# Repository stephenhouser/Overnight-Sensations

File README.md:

# Overnight Sensation Speakers

This repository contains my build plans for [Paul Carmody](https://sites.google.com/site/undefinition/diy?authuser=0)'s **Overnight Sensations** speakers. It is intended to compliment Paul's designs, plans, and notes with manufacturable components. That is herein lie full CNC-able and PCB-producable components.

This currently includes details for the [original bookshelf speakers](https://sites.google.com/site/undefinition/bookshelf-speakers/diy-overnightsensations), the [floorstanding TMM's](https://sites.google.com/site/undefinition/floorstanding-speakers/overnightsensationtmm?authuser=0), and the [center speaker](https://sites.google.com/site/undefinition/home-theater-speakers/overnightsensationcenterchannelbipolewhatwhen?authuser=0). I have future plans to include the [surround speakers](https://sites.google.com/site/undefinition/home-theater-speakers/overnightsensationcenterchannelbipolewhatwhen?authuser=0).

This is a work in progress, bear with me as I build the speakers and add the components.

### A few notes on the designs

- Designed for 1/2" material. Using the 1/2" plans in all cases.
- Uses miter joints at the box corners, so can use already faced plywood.
- Uses painted MDF for the baffle. Could use faced plywood but the fillet on the outside edges would need to be removed.
- Does not use rabbet for back. Seems an overly complicated addition.

If you are using something else, it should be easily adapted.

## Bookshelf TM

No build files available.

I built these a few years ago and did not document things very well, save for a few photos and the build documents.

## Floorstanding TMM

Includes:

- Cabinet Plans in FreeCAD
- Crossover PCB in KiCad with Gerbers for PCB manufacture
- 2"x3" port in FreeCAD for 3D printing

These are the most well developed plans as they are the most recent I've worked on.

NOTE: The version I have designed for uses the HiVi T20 tweeter and 1/2" thick wood for the cabinet. I've made some attempt at making the design general and adaptable, but you will likely have to tweak if you build the alternate version.

The cabinet design was reproduced from Paul's SketchUp screen capture into FreeCAD. The full FreeCAD files are in the [floorstanding[(floorstading)] directory. Here's a snapshot of the major dimensions. Perhaps enough to build from.

My crossover PCB is for the HiVi T20 tweeter. You can use the same PCB, just substitute the different value components.

**NOTE**: I started working on alternate crossovers with thicker traces but stopped. See the notes below about **Power Handling**. I think the 3mm traces I have are "thick enough" for this configuration under normal use. It would be nice to have thicker traces (5-6mm), and 9.5mm spaced screw terminals. If I ever do make another PCB, I'll make those changes. Oh, I also forgot to put in additional holes for the wire ties on the 1.5 mH coil.

## Center MMTM

Next to be built!

## Surround

Yet to be built!

## Software Tools

I use the following software in the production of these. These are all open-source freely available products.

- [Inkscape](https://inkscape.org) for basic drawing and to generate SVG files for patterns.
- [KiCad](https://www.kicad.org) for schematic capture and PCB design.
- [FreeCAD](https://www.freecad.org) for cabinet design and CAM toolpath generation.
- [LibreOffice](https://www.libreoffice.org) for spreadsheets, bill of materials (BOM).

In the past I used the following software in parts of the process but am quickly moving away from them as I migrate to FreeCAD and other more open and interchangable software.

- [Carbide Create](https://carbide3d.com/carbidecreate/) / [Carbide Motion](https://carbide3d.com/carbidemotion/) for 2D CAD/CAM on Shapeoko 3
- [Autodesk Fusion 360](no link, autodesk keeps taking features away and I don't want to support that) for cabinet design and CAM toolpath generation

## Power Handling

To calculate what the power rating of the speaker is, and the appropriate trace width for the crossover boards.

- HiVi B4N is rated 25W RMS (50W max) at 8 Ohms, 60 - 4,000 Hz
- HiVi B3N is rated 10W RMS (30W max) at 8 Ohms, 80 - 12,000 Hz
- HiVi T20-8 is rated 15W RMS (no max specified) at 8 Ohms, 4,000 - 20,000 Hz

From some random source on the Internet:

    roughly 40-40-20 percentage for woofer, mid, tweeter

From [celestion](https://celestion.com/blog/power-handling-all-you-need-to-know/)

    As a rule of thumb, the cabinet power handling should be calculated as a multiple of the lowest rated speaker. For example in a 2×12 containing a 60-watt speaker and a 30-watt speaker, overall cabinet power handling is 2×30-watt = 60-watt. In a 4×12 containing 2×60-watt speakers and 2×30-watt speakers, overall cabinet power handling is 4×30-watt = 120-watt.

By this measure:

The TMM is either 25*.4+25*.4+14*.2 23W (43W max) or 3x15W = 45W (90W max) into an 8 Ohm speakers. With `I = E/R`, `23/8 = 2.875A` or `43/8 = 5.73A` max.

Using [Digikey Trace Size Calculator](https://www.digikey.com/en/resources/conversion-calculators/conversion-calculator-pcb-trace-width) and looking at "Required Trace Width" for "External Layers in Air":

- 2.7A, 22 degrees-C, 1 Oz weight, 4 inches, 20 degree rise gives **0.78 mm trace width**
- 5.73A max, 22 degrees-C, 1 Oz weight, 4 inches, 20 degree rise gives **2.19mm trace width**

I also calculated voltage drop and resistance of these traces, but not sure how to evaluate these in an objective way. Citations needed.

- 0.78mm trace width, 0.07 Ohms, 0.18V voltage drop, 0.49W power loss
- 2.19mm trace width, 0.02 Ohms, 0.13V voltage drop, 0.79W power loss

## NOTE: About The Files

There may be extraneous generated files in the directories, like generated GCode, Gerber files, and such. These are outputs from processes and may not be suited to your manufacturing equipment. You should regenerate these for your own equipment, don't use mine. I warned you.

The `Common-Crossover` directory is not used. This is a work-in-progress of designing a common crossover PCB that could work on all the Overnight Sensation speakers. It started when I thought my trace widths were not sufficient. **It is incomplete**.

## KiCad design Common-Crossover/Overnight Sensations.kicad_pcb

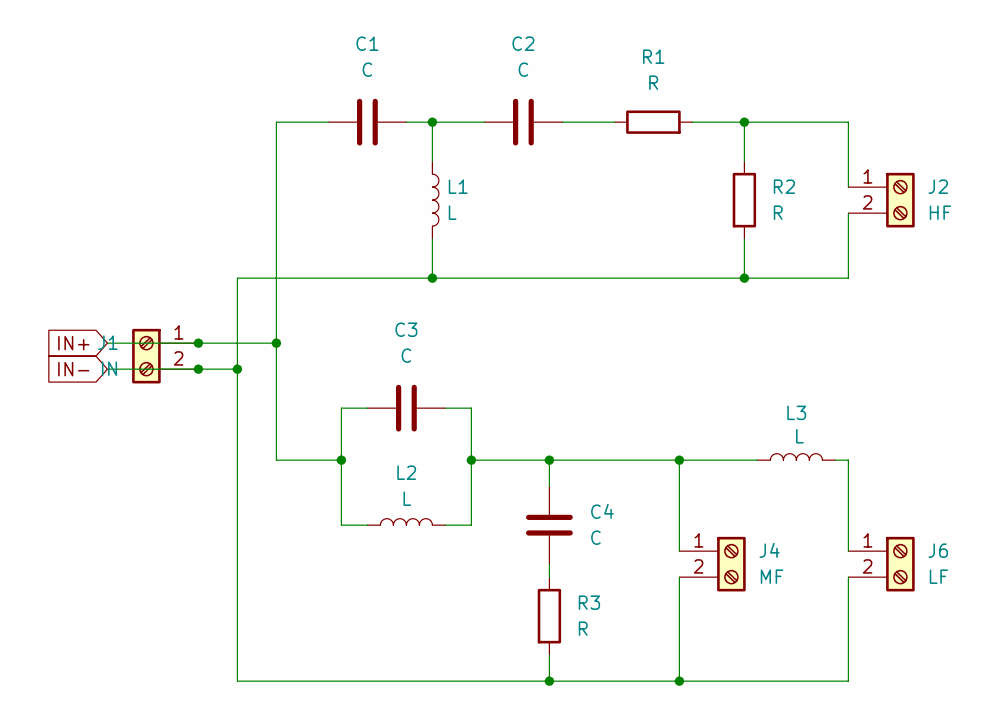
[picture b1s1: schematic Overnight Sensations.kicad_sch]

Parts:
C1, C2: C; C_Audio_31x14
C3: C; C_Audio_18x07
C4: C; C_Audio_45x18
J1: IN; screw_terminal_01x02_p9.5mm
J2: HF; screw_terminal_01x02_p9.5mm
J4: MF; screw_terminal_01x02_p9.5mm
J6: LF; screw_terminal_01x02_p9.5mm
L1: L; L_Audio_D40_W18_Vertical
L2: L; L_Audio_D48_W16_Horizontal
L3: L; L_Audio_61x38_Iron
R1, R2, R3: R; R_Axial_Power_L48.0mm_W12.5mm_P55.88mm

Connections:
IN+: C1.1, C3.1, J1.1, L2.1
IN-: J1.2, J2.2, J4.2, J6.2, L1.2, R2.2, R3.2
unnamed: C1.2, C2.1, L1.1
unnamed: C2.2, R1.1
unnamed: C4.2, R3.1
unnamed: J2.1, R1.2, R2.1
unnamed: C3.2, C4.1, J4.1, L2.2, L3.2
unnamed: J6.1, L3.1

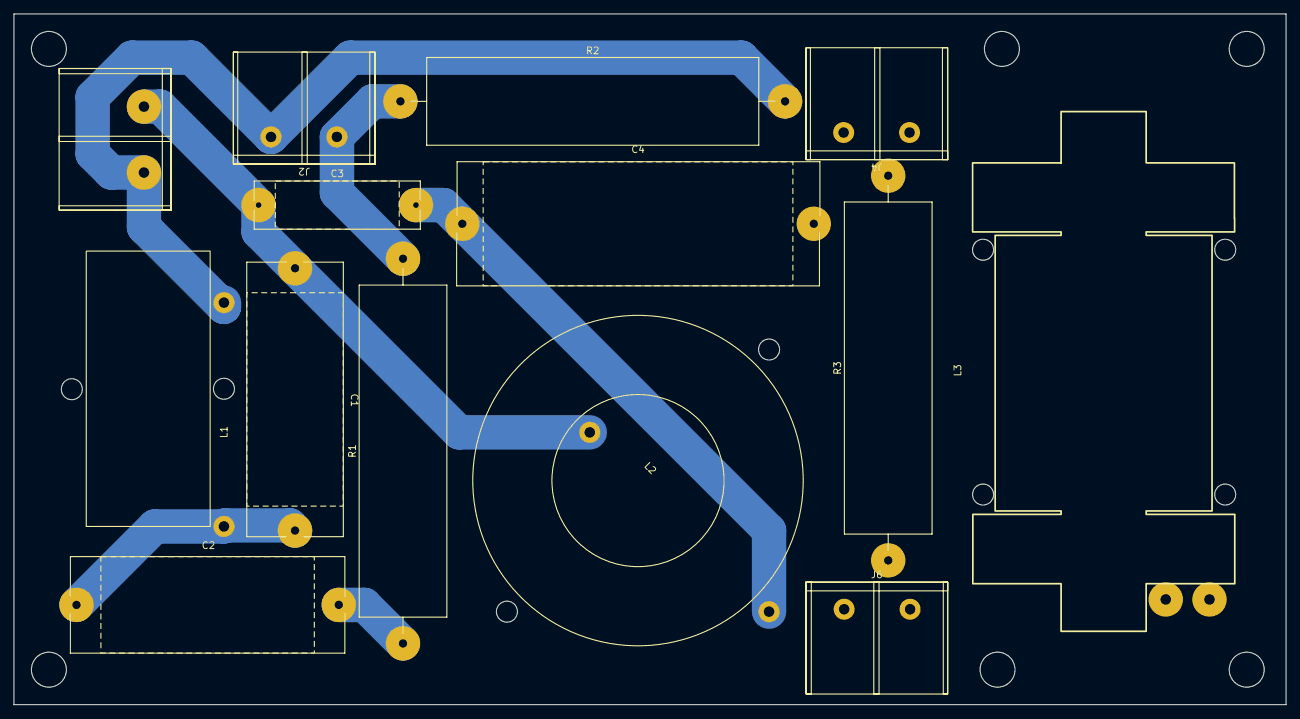
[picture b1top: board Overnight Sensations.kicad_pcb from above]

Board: 2 copper layers, 184.8 x 100.3 mm, 14 parts (0 on the bottom side), 8 nets.

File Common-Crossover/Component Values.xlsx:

Overnight Sensations Crossover Component Values
 | Bookshelf |  |  | Floorstanding |  |  | Center |  |  | Bipole
Component | TM | Length | Diameter | TMM | Length | Diameter | MMTMM | Length | Diameter | Surround | Length | Diameter
C1 | 1.5 | 31 | 11 | 2.2 | 31 | 13 | 2.2 | 31 | 13 | 1.5 | 31 | 11
C2 | 2.2 | 31 | 13 | 2.7 | 31 | 14 | 5.1 | 31 | 21 | 2.2 | 31 | 13
C3 | 0.22 | 18 | 7 | 0.22 | 18 | 7 | --- |  |  | 0.22 | 18 | 7
C4 | 6.8 | 48 | 18 | 6.8 | 48 | 18 | 4.7 | 31 | 19 | 10 | 48 | 22
R1 | 6 | 48 | 10 | 5.1 | 48 | 10 | 1.5 | 48 | 10 | 6 | 48 | 10
R2 | 10 | 48 | 10 | 4.7 | 48 | 10 | 6 | 48 | 10 | ---
R3 | 0 |  |  | 0 |  |  | 1 | 48 | 10 | 0
L1 | 0.35 |  |  | 0.3 |  |  | 0.26 |  |  | 0.35
L2 | 1.1 |  |  | 1.5 |  |  | 1.5 |  |  | 0.9
L3 | --- |  |  | 3.5 |  |  | 3.5 |  |  | ---
J2 | HF |  |  | HF |  |  | HF- |  |  | HF1
J3 | --- |  |  | --- |  |  | --- |  |  | HF2
J4 | MF |  |  | MF |  |  | MF1 |  |  | MF1
J5 | 0 |  |  | 0 |  |  | MF2 |  |  | 0
J6 | --- |  |  | LF |  |  | LF1 |  |  | MF2
J7 | --- |  |  | 0 |  |  | LF2 |  |  | 0

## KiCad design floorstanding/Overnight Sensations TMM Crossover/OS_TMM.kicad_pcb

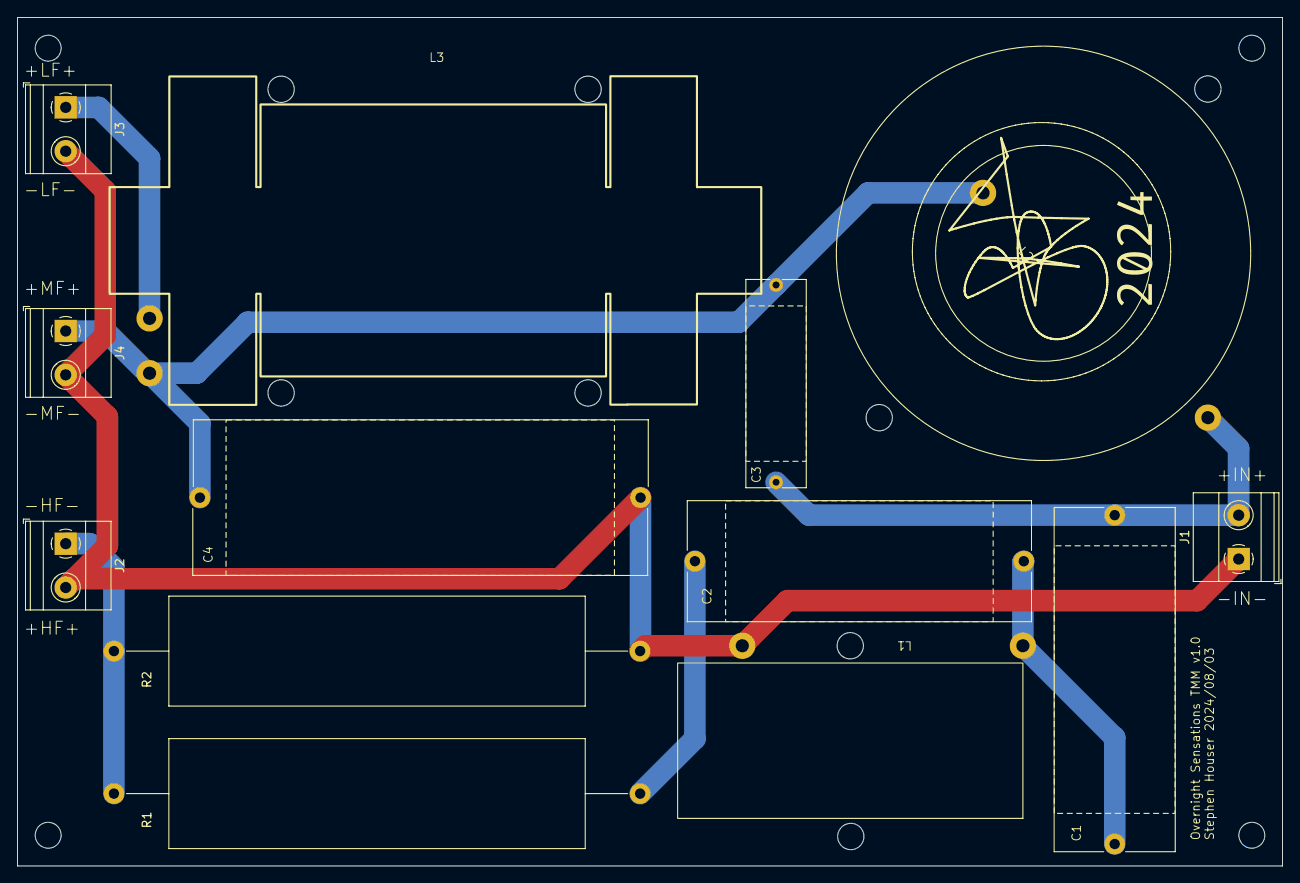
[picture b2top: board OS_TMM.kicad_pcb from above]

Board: 2 copper layers, 146.6 x 98.3 mm, 13 parts (0 on the bottom side), 7 nets.

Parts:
C1: 2.2uF; C_Audio_31x14
C2: 2.7uF; C_Audio_31x14
C3: 0.22uF; C_Audio_18x07
C4: 6.8uF; C_Audio_45x18
J1: In; TerminalBlock_Phoenix_MKDS-1,5-2-5.08_1x02_P5.08mm_Horizont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
J2: High; TerminalBlock_Phoenix_MKDS-1,5-2-5.08_1x02_P5.08mm_Horizont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
J3: Low; TerminalBlock_Phoenix_MKDS-1,5-2-5.08_1x02_P5.08mm_Horizont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
J4: Mid; TerminalBlock_Phoenix_MKDS-1,5-2-5.08_1x02_P5.08mm_Horizont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
L1: 0.30mH; L_Audio_D40_W18_Vertical
L2: 1.5mH; L_Audio_D48_W16_Horizontal
L3: 3.5mH; L_Audio_61x38_Iron
R1: 5.1; R_Axial_Power_L48.0mm_W12.5mm_P60.96mm
R2: 4.7; R_Axial_Power_L48.0mm_W12.5mm_P60.96mm

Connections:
HF+: C4.2, J1.1, J2.2, J3.2, J4.2, L1.2, R2.2
HF-: J2.1, R1.1, R2.1
IN+: C1.2, C3.2, J1.2, L2.2
LOW+: J3.1, L3.1
MID+: C3.1, C4.1, J4.1, L2.1, L3.2
unnamed: C1.1, C2.2, L1.1
unnamed: C2.1, R1.2

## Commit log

2024-08-06 update readme images
2024-08-06 add center cad design
2024-08-06 gitignore
2024-08-06 add center and center drawing
2024-08-06 typo in filename
2024-08-06 new center drawing
2024-08-12 update readme with note about corssover
2024-08-19 update readme, add common-crossover (not used)
2024-08-19 update readme about common-crossover directory
2024-08-20 add glamor shot of tmm's
2024-08-20 really add readme
2024-08-20 rotate images
2024-08-20 replace with png
2026-02-17 update, add OS freecad start
2026-02-17 add notes on sub
